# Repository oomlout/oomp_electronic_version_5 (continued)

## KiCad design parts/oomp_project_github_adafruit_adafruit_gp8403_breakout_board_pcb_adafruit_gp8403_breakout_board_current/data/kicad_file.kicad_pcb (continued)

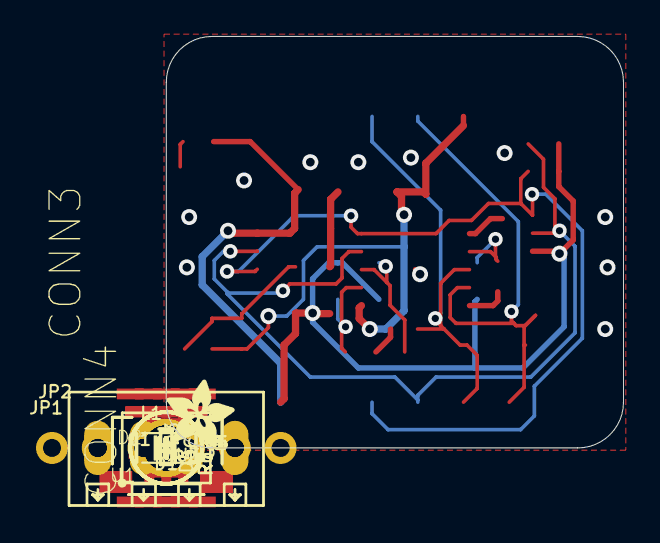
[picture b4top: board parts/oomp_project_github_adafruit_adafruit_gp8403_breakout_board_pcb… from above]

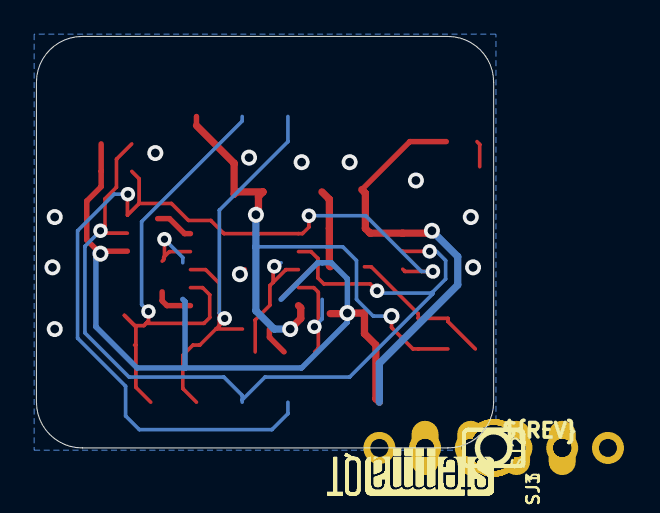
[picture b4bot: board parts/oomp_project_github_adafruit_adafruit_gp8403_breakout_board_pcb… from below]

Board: 2 copper layers, 25.4 x 22.9 mm, 61 parts (17 on the bottom side), 14 nets.

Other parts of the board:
PLABEL0: PLABEL0
PLABEL1: PLABEL1
PLABEL2: PLABEL2
PLABEL3: PLABEL3
PLABEL4: PLABEL4
PLABEL5: PLABEL5
PLABEL6: PLABEL6
PLABEL7: PLABEL7
PLABEL8: PLABEL8
PLABEL9: PLABEL9
PLABEL10: PLABEL10
PLABEL11: PLABEL11
PLABEL12: PLABEL12
PLABEL13: PLABEL13
PLABEL14: PLABEL14
PLABEL15: PLABEL15
PLABEL16: PLABEL16
PLABEL17: PLABEL17
PLABEL18: PLABEL18
PLABEL19: PLABEL19
PLABEL20: PLABEL20
PLABEL21: PLABEL21
U$9: ADAFRUIT_3.5MM
U$25: PCBFEAT-REV-040
U$30, U$31: STEMMAQT

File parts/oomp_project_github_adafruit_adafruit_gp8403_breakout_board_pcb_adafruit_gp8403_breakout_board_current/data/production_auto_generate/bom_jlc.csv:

Comment,Designator,Footprint,LCSC Part #
,JP1,Adafruit GP8403 Breakout Board rev B-import-fps:1X06_ROUND_70,C37208
,U$9,Adafruit GP8403 Breakout Board rev B-import-fps:ADAFRUIT_3.5MM,
,U$25,Adafruit GP8403 Breakout Board rev B-import-fps:PCBFEAT-REV-040,
,PLABEL0,Adafruit GP8403 Breakout Board rev B-import-fps:PLABEL0,
,PLABEL1,Adafruit GP8403 Breakout Board rev B-import-fps:PLABEL1,
,PLABEL10,Adafruit GP8403 Breakout Board rev B-import-fps:PLABEL10,
,PLABEL11,Adafruit GP8403 Breakout Board rev B-import-fps:PLABEL11,
,PLABEL12,Adafruit GP8403 Breakout Board rev B-import-fps:PLABEL12,
,PLABEL13,Adafruit GP8403 Breakout Board rev B-import-fps:PLABEL13,
,PLABEL14,Adafruit GP8403 Breakout Board rev B-import-fps:PLABEL14,
,PLABEL15,Adafruit GP8403 Breakout Board rev B-import-fps:PLABEL15,
,PLABEL16,Adafruit GP8403 Breakout Board rev B-import-fps:PLABEL16,
,PLABEL17,Adafruit GP8403 Breakout Board rev B-import-fps:PLABEL17,
,PLABEL18,Adafruit GP8403 Breakout Board rev B-import-fps:PLABEL18,
,PLABEL19,Adafruit GP8403 Breakout Board rev B-import-fps:PLABEL19,
,PLABEL2,Adafruit GP8403 Breakout Board rev B-import-fps:PLABEL2,
,PLABEL20,Adafruit GP8403 Breakout Board rev B-import-fps:PLABEL20,
,PLABEL21,Adafruit GP8403 Breakout Board rev B-import-fps:PLABEL21,
,PLABEL3,Adafruit GP8403 Breakout Board rev B-import-fps:PLABEL3,
,PLABEL4,Adafruit GP8403 Breakout Board rev B-import-fps:PLABEL4,
,PLABEL5,Adafruit GP8403 Breakout Board rev B-import-fps:PLABEL5,
,PLABEL6,Adafruit GP8403 Breakout Board rev B-import-fps:PLABEL6,
,PLABEL7,Adafruit GP8403 Breakout Board rev B-import-fps:PLABEL7,
,PLABEL8,Adafruit GP8403 Breakout Board rev B-import-fps:PLABEL8,
,PLABEL9,Adafruit GP8403 Breakout Board rev B-import-fps:PLABEL9,
,"U$30,U$31",Adafruit GP8403 Breakout Board rev B-import-fps:STEMMAQT,
0.1uF,C1,Adafruit GP8403 Breakout Board rev B-import-fps:0603-NO,C14663
10K,"R1,R2,R3,R4,R5,R7,R8",Adafruit GP8403 Breakout Board rev B-import-fps:0603-NO,C98220
10uF,"C2,C4,C5,C6",Adafruit GP8403 Breakout Board rev B-import-fps:0805-NO,
10uH,L1,Adafruit GP8403 Breakout Board rev B-import-fps:INDUCTOR_1007,
1x4 2.54mm,JP2,Adafruit GP8403 Breakout Board rev B-import-fps:1X04_2.54MMTERMINAL,C42431795
2.2uF,C3,Adafruit GP8403 Breakout Board rev B-import-fps:0603-NO,C23630
22pF,C8,Adafruit GP8403 Breakout Board rev B-import-fps:0603-NO,C105620
87.6k,R6,Adafruit GP8403 Breakout Board rev B-import-fps:0603-NO,
GP8403,U1,Adafruit GP8403 Breakout Board rev B-import-fps:ESSOP10-EP,
GREEN,D1,Adafruit GP8403 Breakout Board rev B-import-fps:CHIPLED_0603_NOOUTLINE,
H12VND5U,"D3,D4",Adafruit GP8403 Breakout Board rev B-import-fps:SOD-523,
MBR0540,D2,Adafruit GP8403 Breakout Board rev B-import-fps:SOD-123FL,
STEMMA_I2C_QT,"CONN3,CONN4",Adafruit GP8403 Breakout Board rev B-import-fps:JST_SH4,C160404
TPS61040,U3,Adafruit GP8403 Breakout Board rev B-import-fps:SOT23-5,

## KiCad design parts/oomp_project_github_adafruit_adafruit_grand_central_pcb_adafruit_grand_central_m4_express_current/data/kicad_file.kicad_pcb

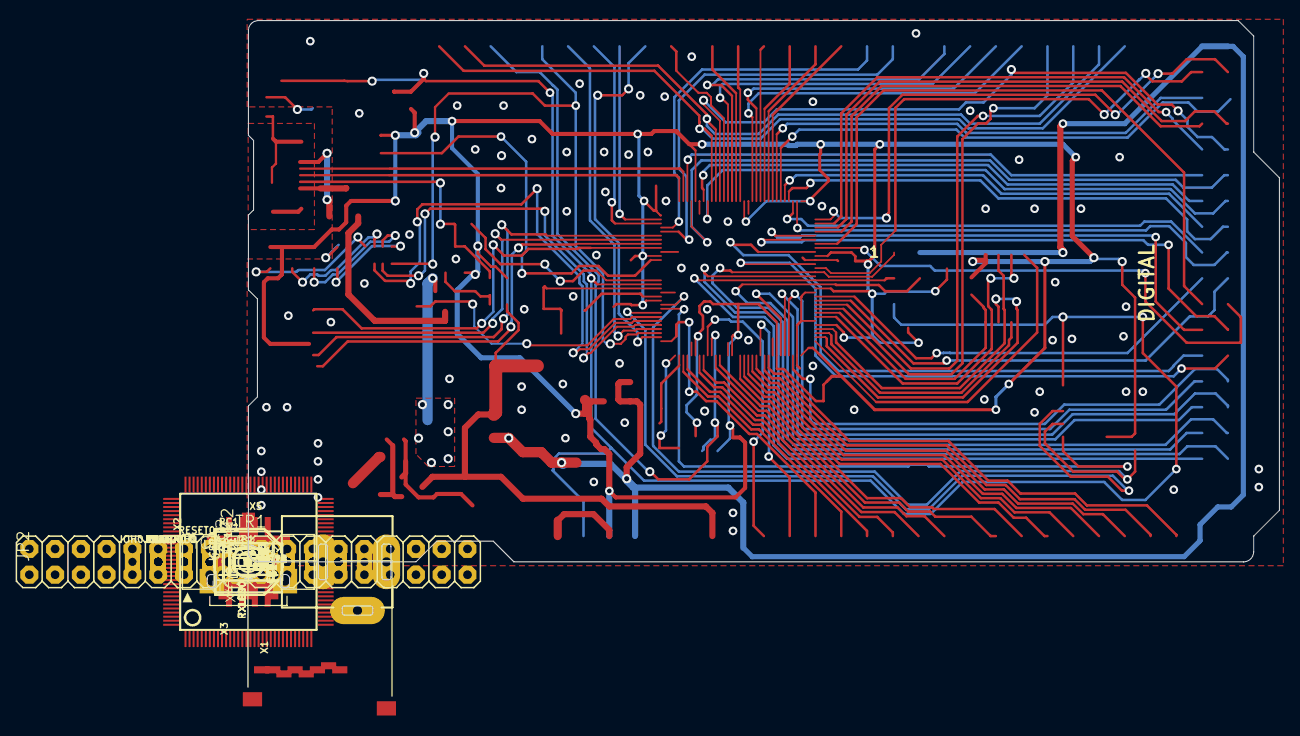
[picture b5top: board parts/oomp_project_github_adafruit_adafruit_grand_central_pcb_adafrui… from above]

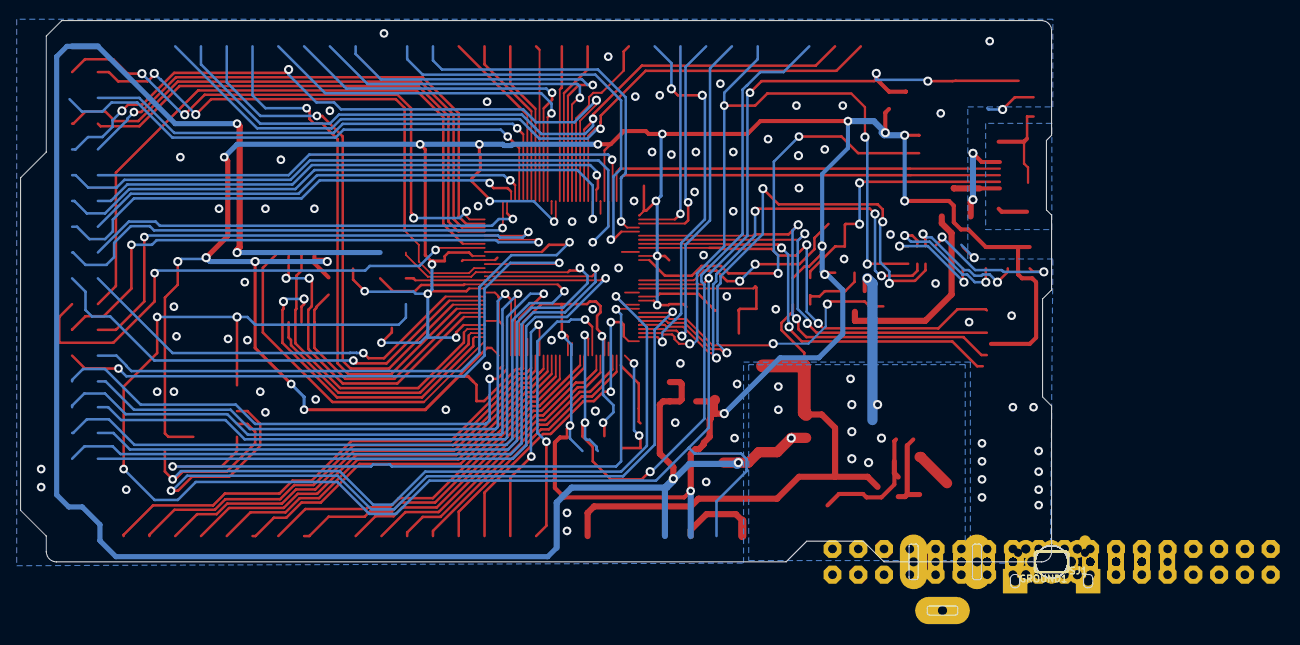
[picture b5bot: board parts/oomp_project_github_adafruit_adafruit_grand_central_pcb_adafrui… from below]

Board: 2 copper layers, 105.7 x 58.6 mm, 81 parts (3 on the bottom side), 113 nets.

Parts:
ANALOGH0: 20610; 1X08_OVALWAVE
ANALOGL0: 20610; 1X08_OVALWAVE
C1, C2, C3: 10uF; 0805-NO
C4, C6, C8, C10, C11, C14, C15, C16, C18, C19, C20, C21, C22, C23, C24, C25: .1u; 0603-NO
C5, C7: 22pF; 0603-NO
C9: 1uF; 0603-NO
C12, C13, C17: 0.1uF; 0603-NO
D1: MBR120; SOD-123
F2: 500mA; R1206
FB2: FERRITE; 0805-NO
FD1, FD2, FD3, FD4, FD5: FIDUCIAL_1MM
GROUND1: SOLDERJUMPER_CLOSEDWIRE
IC3: 74LVC1G125D; SOT23-5
ICSP0: 3x2 M; 2X03_ROUND_70MIL
IOH0: 20611; 1X10_OVALWAVE
IOL0: 20610; 1X08_OVALWAVE
JP1: 1X01_ROUND
JP2: 2X18_THICKWAVE
L0: RED; CHIPLED_0805_NOOUTLINE
L1: 10uH; INDUCTOR_1007
LED1: WS2812B3535; LED3535
ON0: GREEN; CHIPLED_0805_NOOUTLINE
PC1: 47uF/25V; PANASONIC_D
PC2: 47uF+/6.3V+; PANASONIC_D
POWER0: 20610; 1X08_OVALWAVE
R1: 100K; RESPACK_4X0603
R2: 1K; RESPACK_4X0603
R3, R5, R7: 10K; 0603-NO
R4: 1K; 0603-NO
R11: 330R; 0603-NO
RESET0: EVQQ 6mm; EVQ-Q2_SMALLER
RXLED0: YELLOW; CHIPLED_0805_NOOUTLINE
SJ1: AREF_3V; SOLDERJUMPER_CLOSEDWIRE
SW1: SPDT_SMT_SSSS811101
T2: DMP3098L-7; SOT-23
TR1: DMP3098L-7; SOT-23
TXLED0: YELLOW; CHIPLED_0805_NOOUTLINE
U1: NCP1117ST50T3G; SOT223-R
U2: AP2112K-3.3; SOT23-DBV
U3: GD25Q64; SOIC8_208MIL
U$1: SAMD51PXXA; SQFP-S-14X14-128
U$23: GRANDCENTRAL_REVB-BOT
U$30: GRANDCENTRAL_REVB_TOP
UART0: 20610; 1X08_OVALWAVE
UNK_HOLE_0: dummyfp0
UNK_HOLE_1: dummyfp1
UNK_HOLE_2: dummyfp2
UNK_HOLE_3: dummyfp3
UNK_HOLE_4: dummyfp4
UNK_HOLE_5: dummyfp5
X1: microsd; MICROSD
X2: 2x5 0.05" SWD; 2X05_1.27MM_BOX_POSTS
X3: 20329; 4UCONN_20329_V2
X4: 32.768; XTAL3215
X5: 2.1mm; DCJACK_2MM_PTH

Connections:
3.3V: C3.2, C6.2, C10.2, C11.2, C13.1, C14.2, C15.2, C16.2, C18.2, C19.2, C20.2, C21.2, C22.2, C23.2, C24.2, C25.2, IC3.5, LED1.2, ON0.A, POWER0.2, POWER0.4, R1.4, R3.1, R4.2, R5.2, RXLED0.A, SJ1.1, TXLED0.A, U2.5, U3.8, U$1.6, U$1.15, U$1.26, U$1.32, U$1.37, U$1.46, U$1.54, U$1.65, U$1.79, U$1.91, U$1.97, U$1.107, U$1.118, X1.4, X2.1
+5V: C2.2, ICSP0.2, JP2.1, JP2.2, PC2.+, POWER0.5, TR1.2, U1.2, U1.4, U2.1, U2.3
A0: ANALOGL0.1, U$1.9
A1: ANALOGL0.2, U$1.22
A2: ANALOGL0.3, U$1.128
A3: ANALOGL0.4, U$1.3
A4: ANALOGL0.5, U$1.4
A5: ANALOGL0.6, U$1.7
A6: ANALOGL0.7, U$1.8
A7: ANALOGL0.8, U$1.11
A8: ANALOGH0.1, U$1.12
A9: ANALOGH0.2, U$1.17
A10: ANALOGH0.3, U$1.18
A11: ANALOGH0.4, U$1.19
A12: ANALOGH0.5, U$1.20
A13: ANALOGH0.6, U$1.21
A14: ANALOGH0.7, U$1.23
A15: ANALOGH0.8, U$1.24
AREF: C4.1, IOH0.3, SJ1.2, U$1.10
D0: IOL0.8, U$1.101
D1: IOL0.7, U$1.100
D2: IOL0.6, U$1.72
D3: IOL0.5, U$1.73
D4: IOL0.4, U$1.74
D5: IOL0.3, U$1.75
D6: IOL0.2, U$1.80
D7: IOL0.1, U$1.81
D8: IOH0.10, U$1.84
D9: IOH0.9, U$1.127
D10: IOH0.8, U$1.98
D11: IOH0.7, U$1.99
D12: IOH0.6, U$1.125
D13: IOH0.5, R2.8, U$1.126
D22: JP2.3, U$1.51
D23: JP2.4, U$1.63
D44: JP2.25, U$1.55
D45: JP2.26, U$1.52
D46: JP2.27, U$1.29
D47: JP2.28, U$1.30
D48: JP2.29, U$1.27
D49: JP2.30, U$1.28
D+: U$1.95, X3.D+
D-: U$1.94, X3.D-
FLASH_CS: R5.1, U3.1, U$1.40
FLASH_IO0: U3.5, U$1.33
FLASH_IO1: U3.2, U$1.34
FLASH_IO2: U3.3, U$1.35
FLASH_IO3: U3.7, U$1.36
FLASH_SCK: U3.6, U$1.39
GND: C1.2, C2.1, C3.1, C4.2, C5.2, C6.1, C7.2, C8.1, C9.2, C10.1, C11.1, C12.2, C13.2, C14.1, C15.1, C16.1, C17.1, C18.1, C19.1, C20.1, C21.1, C22.1, C23.1, C24.1, C25.1, GROUND1.2, IC3.3, ICSP0.6, IOH0.4, JP2.35, JP2.36, L0.C, LED1.4, PC1.-, PC2.-, POWER0.6, POWER0.7, R1.2, R2.5, RESET0.A, RESET0.A', SW1.A, U1.1, U2.2, U3.4, U$1.5, U$1.14, U$1.25, U$1.31, U$1.38, U$1.45, U$1.53, U$1.64, U$1.78, U$1.90, U$1.96, U$1.106, U$1.116, X1.6, X1.MT1, X1.MT2, X2.3, X2.5, X3.GND, X5.GND, X5.GNDBREAK
MISO: ICSP0.1, JP2.31, U$1.50
MOSI: ICSP0.4, JP2.32, U$1.47
unnamed: L0.A, R2.1
unnamed: FB2.1, GROUND1.1
unnamed: ON0.C, R2.4
unnamed: L1.P$2, U$1.117
unnamed: R2.2, RXLED0.C
unnamed: R2.3, TXLED0.C
unnamed: C5.1, U$1.1, X4.P$1
unnamed: IC3.1, IC3.2, R1.5, R11.1, X3.ID
unnamed: IC3.4, R1.7, R1.8, TR1.3
unnamed: C7.1, U$1.2, X4.P$2
unnamed: D1.C, R7.2, T2.2
NEOPIX: LED1.1, U$1.108
PCC_CLK: JP2.9, U$1.62
PCC_D0: JP2.18, U$1.66
PCC_D1: JP2.17, U$1.67
PCC_D2: JP2.16, U$1.68
PCC_D3: JP2.15, U$1.69
PCC_D4: JP2.14, U$1.88
PCC_D5: JP2.13, U$1.89
PCC_D6: JP2.12, U$1.92
PCC_D7: JP2.11, U$1.93
PCC_D8: JP2.20, U$1.43
PCC_D9: JP2.19, U$1.44
PCC_D10: JP2.22, U$1.56
PCC_D11: JP2.21, U$1.57
PCC_D12: JP2.24, U$1.58
PCC_D13: JP2.23, U$1.59
PCC_DEN1: JP2.7, U$1.60
PCC_DEN2: JP2.8, U$1.61
PCC_XCLK: JP2.10, U$1.85
PWRIN: D1.A, X5.PWR
PWR_SWITCH: JP1.1, R7.1, SW1.B, T2.3
RXLED: R2.7, U$1.124
SCK: ICSP0.3, JP2.33, U$1.48
SCL: IOH0.1, U$1.87, UART0.8
SCL_1: JP2.5, U$1.71
SDA: IOH0.2, U$1.86, UART0.7
SDA_1: JP2.6, U$1.70
SD_CD: U$1.122, X1.CD1
SD_CS: U$1.104, X1.2
SD_MISO: U$1.105, X1.7
SD_MOSI: U$1.102, X1.3
SD_SCK: U$1.103, X1.5
SS: JP2.34, U$1.49
SWCLK: R4.1, U$1.119, X2.4
SWDIO: U$1.120, X2.2
SWO: U$1.121, X2.6
TXLED: R2.6, U$1.123
UART1_RX: U$1.42, UART0.6
UART1_TX: U$1.41, UART0.5
UART2_RX: U$1.77, UART0.4
UART2_TX: U$1.76, UART0.3
UART3_RX: U$1.83, UART0.2
UART3_TX: U$1.82, UART0.1
USBVCC: F2.2, TR1.1
USB_HOSTEN: R11.2, U$1.113
USHIELD: FB2.2, X3.BASE@1, X3.BASE@2, X3.SPRT@1, X3.SPRT@2, X3.SPRT@3, X3.SPRT@4
VBUS: F2.1, X3.VBUS
VDDCORE: C1.1, C8.2, C9.1, L1.P$1, U$1.115
VIN: C12.1, PC1.+, POWER0.8, R1.1, T2.1, U1.3
~RESET: C17.2, ICSP0.5, POWER0.3, R3.2, RESET0.B, RESET0.B', U$1.114, X2.10

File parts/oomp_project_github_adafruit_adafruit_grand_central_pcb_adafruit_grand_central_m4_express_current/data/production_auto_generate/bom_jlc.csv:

Comment,Designator,Footprint,LCSC Part #
,JP1,Adafruit Grand Central M4 Express rev B-import-fps:1X01_ROUND,C7501259
,JP2,Adafruit Grand Central M4 Express rev B-import-fps:2X18_THICKWAVE,
,U$23,Adafruit Grand Central M4 Express rev B-import-fps:GRANDCENTRAL_REVB-BOT,
,U$30,Adafruit Grand Central M4 Express rev B-import-fps:GRANDCENTRAL_REVB_TOP,
,GROUND1,Adafruit Grand Central M4 Express rev B-import-fps:SOLDERJUMPER_CLOSEDWIRE,
,SW1,Adafruit Grand Central M4 Express rev B-import-fps:SPDT_SMT_SSSS811101,
.1u,"C4,C6,C8,C10,C11,C14,C15,C16,C18,C19,C20,C21,C22,C23,C24,C25",Adafruit Grand Central M4 Express rev B-import-fps:0603-NO,
0.1uF,"C12,C13,C17",Adafruit Grand Central M4 Express rev B-import-fps:0603-NO,C14663
100K,R1,Adafruit Grand Central M4 Express rev B-import-fps:RESPACK_4X0603,C25803
10K,"R3,R5,R7",Adafruit Grand Central M4 Express rev B-import-fps:0603-NO,C98220
10uF,"C1,C2,C3",Adafruit Grand Central M4 Express rev B-import-fps:0805-NO,
10uH,L1,Adafruit Grand Central M4 Express rev B-import-fps:INDUCTOR_1007,
1K,R4,Adafruit Grand Central M4 Express rev B-import-fps:0603-NO,C2907002
1K,R2,Adafruit Grand Central M4 Express rev B-import-fps:RESPACK_4X0603,C2907002
1uF,C9,Adafruit Grand Central M4 Express rev B-import-fps:0603-NO,C5673
2.1mm,X5,Adafruit Grand Central M4 Express rev B-import-fps:DCJACK_2MM_PTH,
20329,X3,Adafruit Grand Central M4 Express rev B-import-fps:4UCONN_20329_V2,
20610,"ANALOGH0,ANALOGL0,IOL0,POWER0,UART0",Adafruit Grand Central M4 Express rev B-import-fps:1X08_OVALWAVE,C492421
20611,IOH0,Adafruit Grand Central M4 Express rev B-import-fps:1X10_OVALWAVE,C57369
22pF,"C5,C7",Adafruit Grand Central M4 Express rev B-import-fps:0603-NO,C105620
"2x5 0.05"" SWD",X2,Adafruit Grand Central M4 Express rev B-import-fps:2X05_1.27MM_BOX_POSTS,
32.768,X4,Adafruit Grand Central M4 Express rev B-import-fps:XTAL3215,
330R,R11,Adafruit Grand Central M4 Express rev B-import-fps:0603-NO,C2933198
3x2 M,ICSP0,Adafruit Grand Central M4 Express rev B-import-fps:2X03_ROUND_70MIL,
47uF+/6.3V+,PC2,Adafruit Grand Central M4 Express rev B-import-fps:PANASONIC_D,
47uF/25V,PC1,Adafruit Grand Central M4 Express rev B-import-fps:PANASONIC_D,
500mA,F2,Adafruit Grand Central M4 Express rev B-import-fps:R1206,
74LVC1G125D,IC3,Adafruit Grand Central M4 Express rev B-import-fps:SOT23-5,
AP2112K-3.3,U2,Adafruit Grand Central M4 Express rev B-import-fps:SOT23-DBV,
DMP3098L-7,"T2,TR1",Adafruit Grand Central M4 Express rev B-import-fps:SOT-23,
EVQQ 6mm,RESET0,Adafruit Grand Central M4 Express rev B-import-fps:EVQ-Q2_SMALLER,
FERRITE,FB2,Adafruit Grand Central M4 Express rev B-import-fps:0805-NO,
FIDUCIAL_1MM,"FD1,FD2,FD3,FD4,FD5",Adafruit Grand Central M4 Express rev B-import-fps:FIDUCIAL_1MM,
GD25Q64,U3,Adafruit Grand Central M4 Express rev B-import-fps:SOIC8_208MIL,
GREEN,ON0,Adafruit Grand Central M4 Express rev B-import-fps:CHIPLED_0805_NOOUTLINE,
MBR120,D1,Adafruit Grand Central M4 Express rev B-import-fps:SOD-123,
microsd,X1,Adafruit Grand Central M4 Express rev B-import-fps:MICROSD,
NCP1117ST50T3G,U1,Adafruit Grand Central M4 Express rev B-import-fps:SOT223-R,
RED,L0,Adafruit Grand Central M4 Express rev B-import-fps:CHIPLED_0805_NOOUTLINE,
SAMD51PXXA,U$1,Adafruit Grand Central M4 Express rev B-import-fps:SQFP-S-14X14-128,
WS2812B3535,LED1,Adafruit Grand Central M4 Express rev B-import-fps:LED3535,
YELLOW,"RXLED0,TXLED0",Adafruit Grand Central M4 Express rev B-import-fps:CHIPLED_0805_NOOUTLINE,
